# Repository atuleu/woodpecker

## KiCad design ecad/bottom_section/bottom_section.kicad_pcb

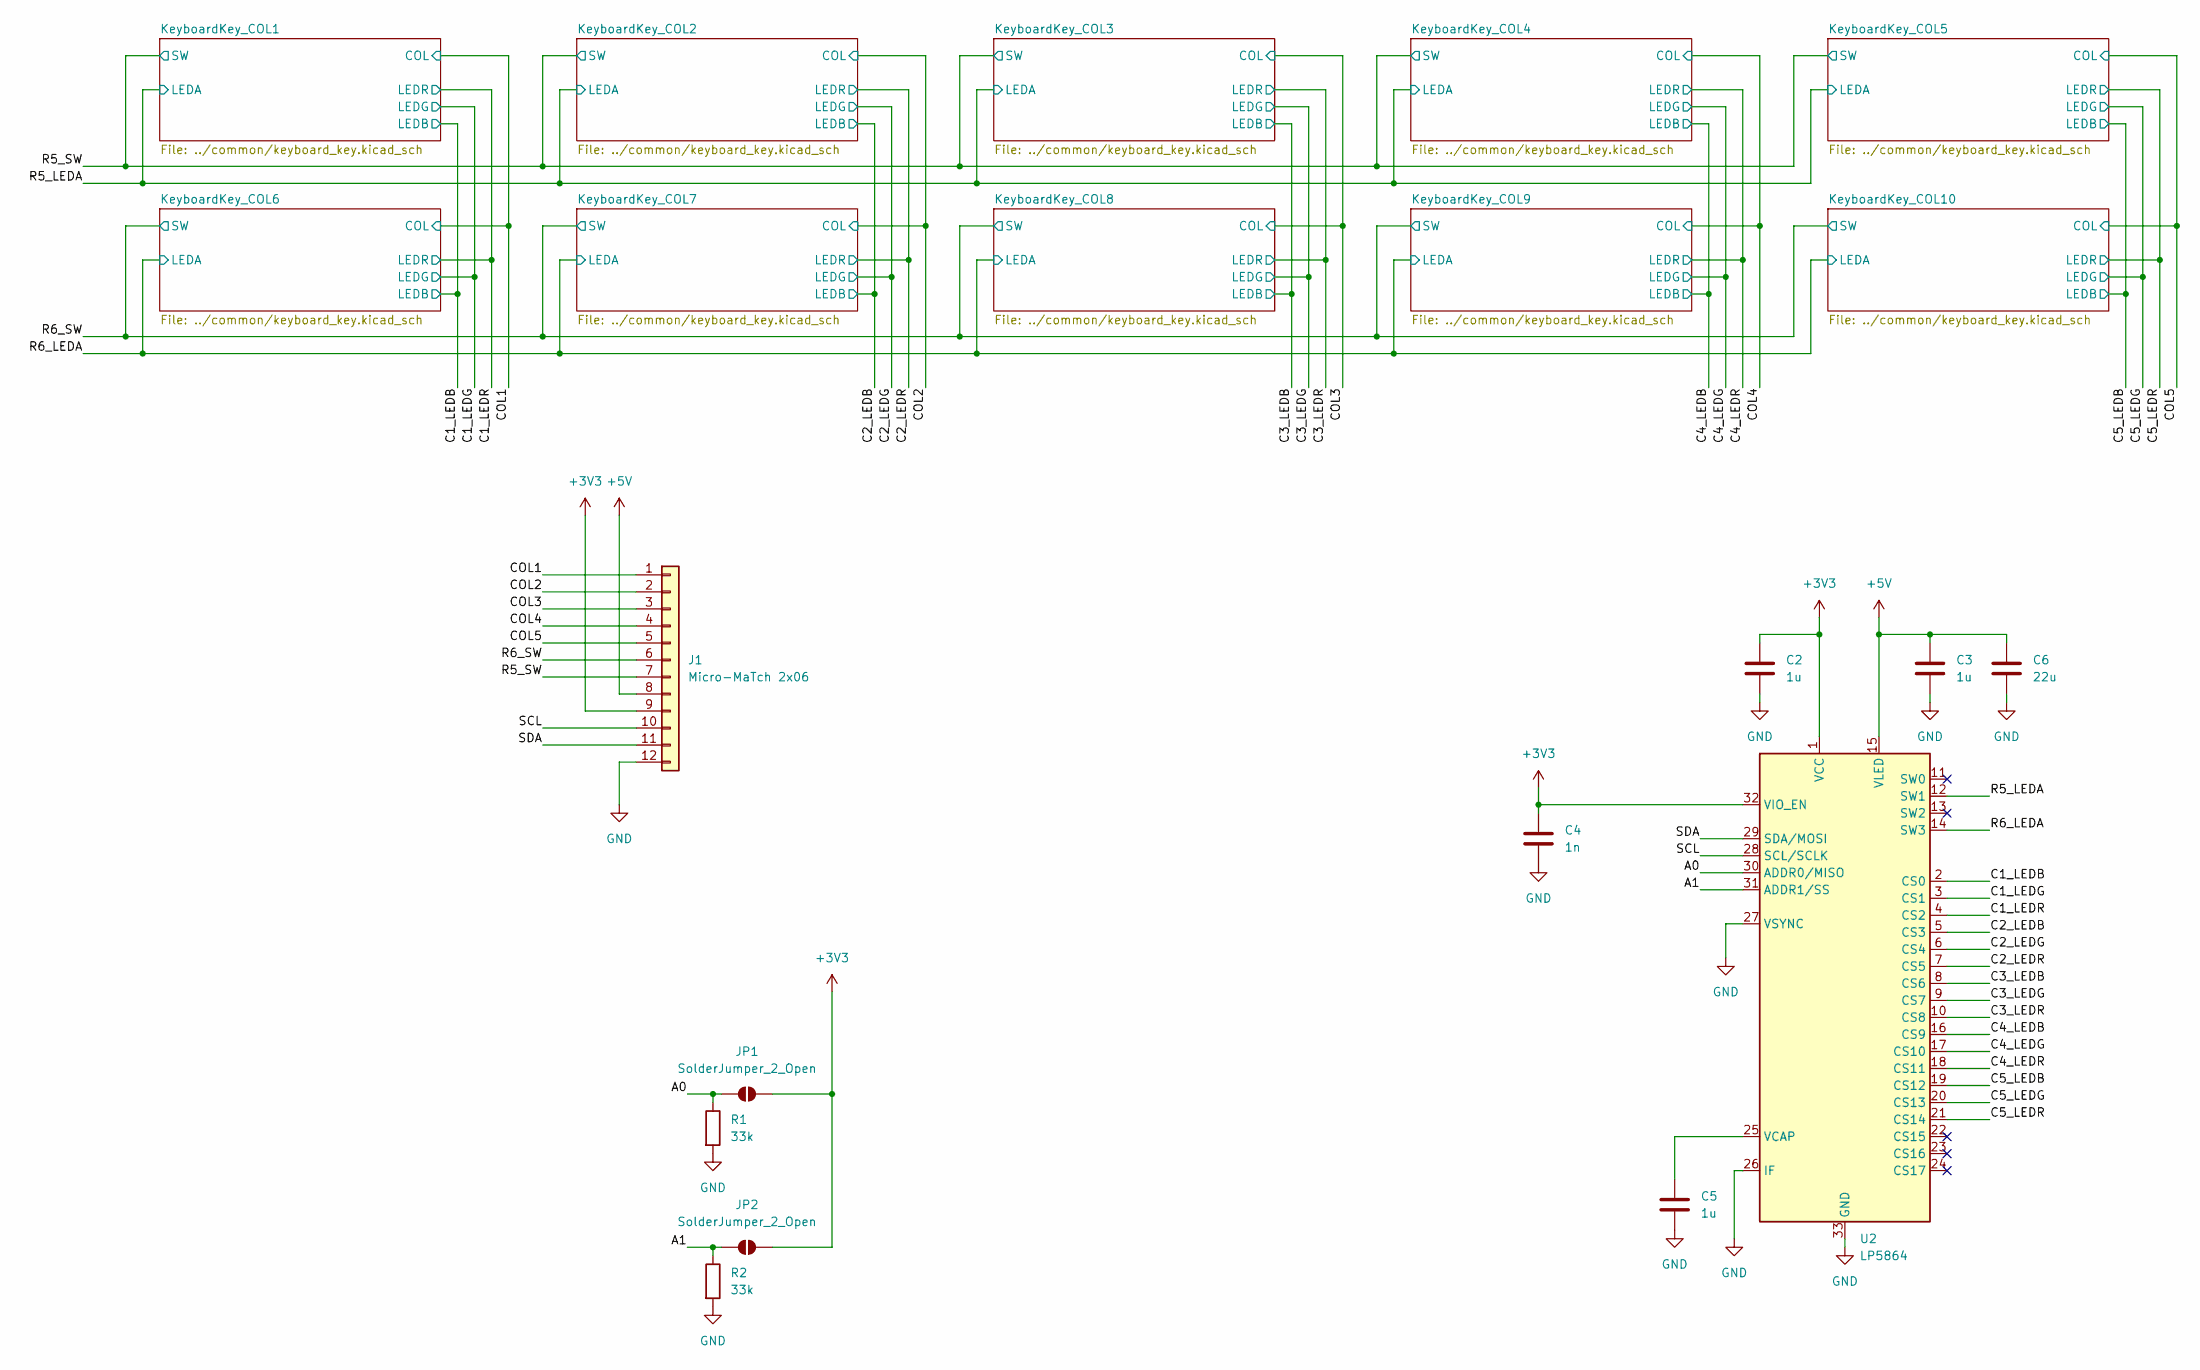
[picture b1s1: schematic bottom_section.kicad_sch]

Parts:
C2, C3, C5: 1u; C_0402_1005Metric; MPN GCM155C71A105KE38D
C4: 1n; C_0402_1005Metric; MPN KGM05AR71A102KH
C6: 22u; C_0805_2012Metric; MPN GRM21BZ71A226ME15L
J1: Micro-MaTch 2x06; TE_Micro-MaTch_1-215079-2_2x06_P1.27mm_Vertical; MPN 1-215079-2
JP1, JP2: SolderJumper_2_Open; SolderJumper-2_P1.3mm_Open_TrianglePad1.0x1.5mm
R1, R2: 33k; R_0603_1608Metric; MPN RC0603FR-0733KL
U2: LP5864; Texas_LP586X_VQFN-32-1EP_4x4mm_P0.4mm_EP2.8x2.8mm_ThermalVi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; MPN LP5864RSMR

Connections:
+3V3: C2.1, C4.1, J1.9, JP1.2 (B), JP2.2 (B), U2.1 (VCC), U2.32 (VIO_EN)
+5V: C3.1, C6.1, J1.8, U2.15 (VLED)
/A0: JP1.1 (A), R1.1, U2.30 (ADDR0/MISO)
/A1: JP2.1 (A), R2.1, U2.31 (ADDR1/SS)
/C1_LEDB: U2.2 (CS0); also elsewhere on the board
/C1_LEDG: U2.3 (CS1); also elsewhere on the board
/C1_LEDR: U2.4 (CS2); also elsewhere on the board
/C2_LEDB: U2.5 (CS3); also elsewhere on the board
/C2_LEDG: U2.6 (CS4); also elsewhere on the board
/C2_LEDR: U2.7 (CS5); also elsewhere on the board
/C3_LEDB: U2.8 (CS6); also elsewhere on the board
/C3_LEDG: U2.9 (CS7); also elsewhere on the board
/C3_LEDR: U2.10 (CS8); also elsewhere on the board
/C4_LEDB: U2.16 (CS9); also elsewhere on the board
/C4_LEDG: U2.17 (CS10); also elsewhere on the board
/C4_LEDR: U2.18 (CS11); also elsewhere on the board
/C5_LEDB: U2.19 (CS12); also elsewhere on the board
/C5_LEDG: U2.20 (CS13); also elsewhere on the board
/C5_LEDR: U2.21 (CS14); also elsewhere on the board
/COL1: J1.1; also elsewhere on the board
/COL2: J1.2; also elsewhere on the board
/COL3: J1.3; also elsewhere on the board
/COL4: J1.4; also elsewhere on the board
/COL5: J1.5; also elsewhere on the board
/R5_LEDA: U2.12 (SW1); also elsewhere on the board
/R5_SW: J1.7; also elsewhere on the board
/R6_LEDA: U2.14 (SW3); also elsewhere on the board
/R6_SW: J1.6; also elsewhere on the board
/SCL: J1.10, U2.28 (SCL/SCLK)
/SDA: J1.11, U2.29 (SDA/MOSI)
GND: C2.2, C3.2, C4.2, C5.2, C6.2, J1.12, R1.2, R2.2, U2.26 (IF), U2.27 (VSYNC), U2.33 (GND)
unnamed: C5.1, U2.25 (VCAP)

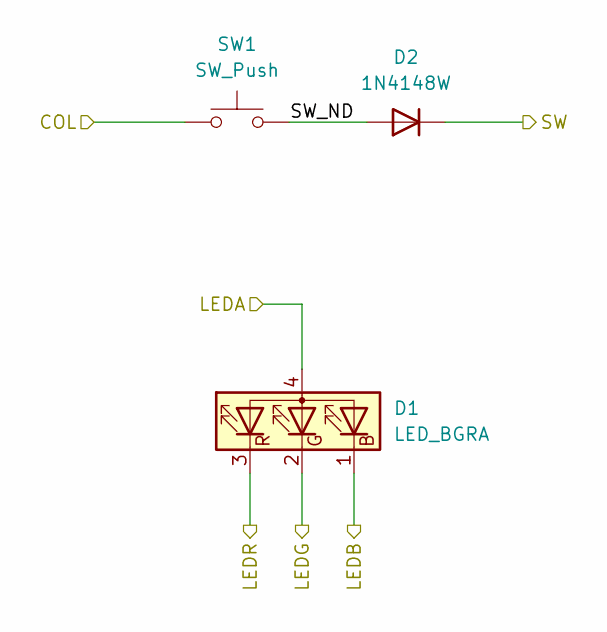
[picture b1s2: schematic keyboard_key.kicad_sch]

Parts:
D1: LED_BGRA; LED_Inolux_IN-PI32TRRRGB_PLCC4_3.2x2.8mm_P1.5mm; MPN IN-P32TRRRGB
D2: 1N4148W; D_SOD-123; MPN 1N4148W
SW1: SW_Push; SW_Hotswap_Kailh_MX_1.00u; MPN 1528-5118-ND

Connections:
/C1_LEDB: D1.1 (BK); also elsewhere on the board
/C1_LEDG: D1.2 (GK); also elsewhere on the board
/C1_LEDR: D1.3 (RK); also elsewhere on the board
/COL1: SW1.1; also elsewhere on the board
/KeyboardKey_COL1/SW_ND: D2.2 (A), SW1.2
/R5_LEDA: D1.4 (A); also elsewhere on the board
/R5_SW: D2.1 (K); also elsewhere on the board

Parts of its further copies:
D4, D6, D8, D10, D12, D14, D16, D18, D20: 1N4148W; D_SOD-123; MPN 1N4148W
D5, D7, D9, D11, D13, D15, D17, D19: LED_BGRA; LED_Inolux_IN-PI32TRRRGB_PLCC4_3.2x2.8mm_P1.5mm; MPN IN-P32TRRRGB
SW2, SW3, SW4, SW5, SW6, SW7, SW8, SW9, SW10: SW_Push; SW_Hotswap_Kailh_MX_1.00u; MPN 1528-5118-ND

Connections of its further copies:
/C1_LEDB: D11.1 (BK); also elsewhere on the board
/C1_LEDG: D11.2 (GK); also elsewhere on the board
/C1_LEDR: D11.3 (RK); also elsewhere on the board
/C2_LEDB: D13.1 (BK); also elsewhere on the board
/C2_LEDG: D13.2 (GK); also elsewhere on the board
/C2_LEDR: D13.3 (RK); also elsewhere on the board
/C3_LEDB: D5.1 (BK), D15.1 (BK); also elsewhere on the board
/C3_LEDG: D5.2 (GK), D15.2 (GK); also elsewhere on the board
/C3_LEDR: D5.3 (RK), D15.3 (RK); also elsewhere on the board
/C4_LEDB: D7.1 (BK), D17.1 (BK); also elsewhere on the board
/C4_LEDG: D7.2 (GK), D17.2 (GK); also elsewhere on the board
/C4_LEDR: D7.3 (RK), D17.3 (RK); also elsewhere on the board
/C5_LEDB: D9.1 (BK), D19.1 (BK); also elsewhere on the board
/C5_LEDG: D9.2 (GK), D19.2 (GK); also elsewhere on the board
/C5_LEDR: D9.3 (RK), D19.3 (RK); also elsewhere on the board
/COL1: SW6.1; also elsewhere on the board
/COL2: SW2.1, SW7.1; also elsewhere on the board
/COL3: SW3.1, SW8.1; also elsewhere on the board
/COL4: SW4.1, SW9.1; also elsewhere on the board
/COL5: SW5.1, SW10.1; also elsewhere on the board
/KeyboardKey_COL2/SW_ND: D4.2 (A), SW2.2
/KeyboardKey_COL3/SW_ND: D6.2 (A), SW3.2
/KeyboardKey_COL4/SW_ND: D8.2 (A), SW4.2
/KeyboardKey_COL5/SW_ND: D10.2 (A), SW5.2
/KeyboardKey_COL6/SW_ND: D12.2 (A), SW6.2
/KeyboardKey_COL7/SW_ND: D14.2 (A), SW7.2
/KeyboardKey_COL8/SW_ND: D16.2 (A), SW8.2
/KeyboardKey_COL9/SW_ND: D18.2 (A), SW9.2
/KeyboardKey_COL10/SW_ND: D20.2 (A), SW10.2
/R5_LEDA: D5.4 (A), D7.4 (A), D9.4 (A); also elsewhere on the board
/R5_SW: D4.1 (K), D6.1 (K), D8.1 (K), D10.1 (K); also elsewhere on the board
/R6_LEDA: D11.4 (A), D13.4 (A), D15.4 (A), D17.4 (A), D19.4 (A); also elsewhere on the board
/R6_SW: D12.1 (K), D14.1 (K), D16.1 (K), D18.1 (K), D20.1 (K); also elsewhere on the board

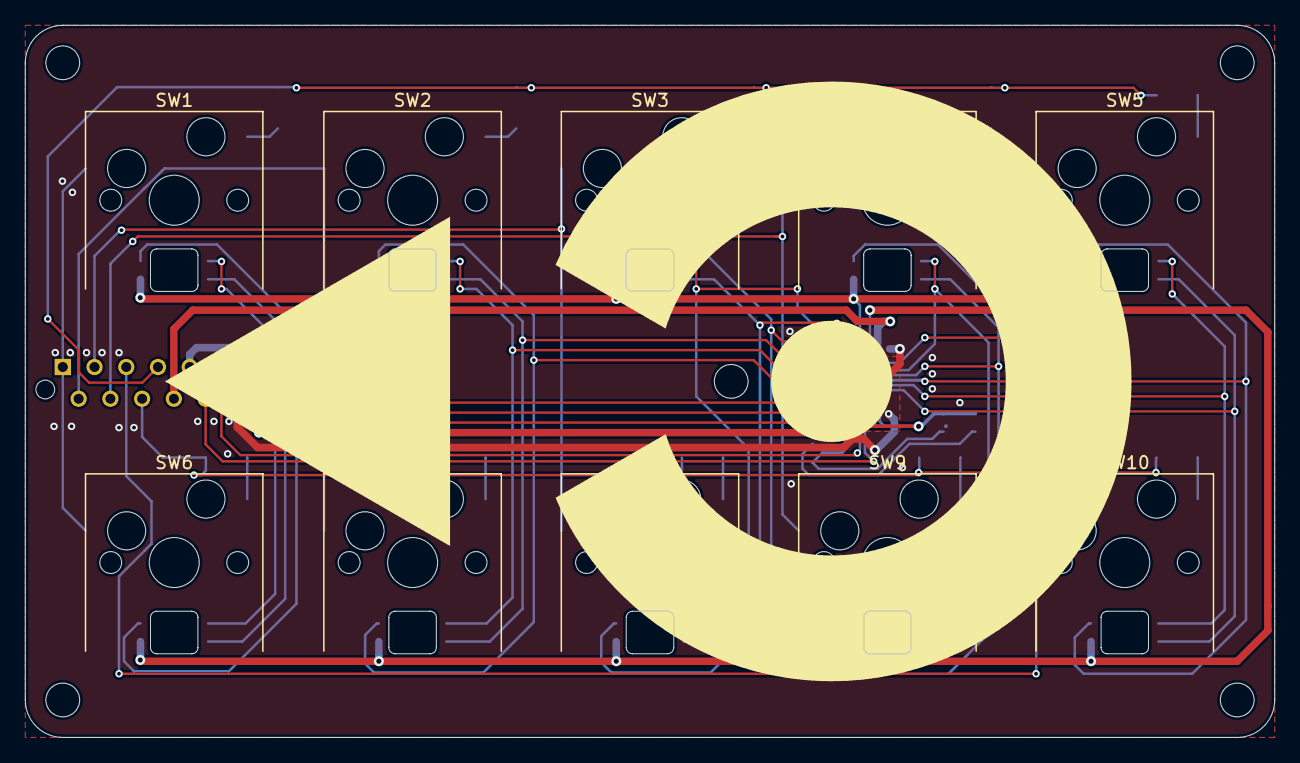
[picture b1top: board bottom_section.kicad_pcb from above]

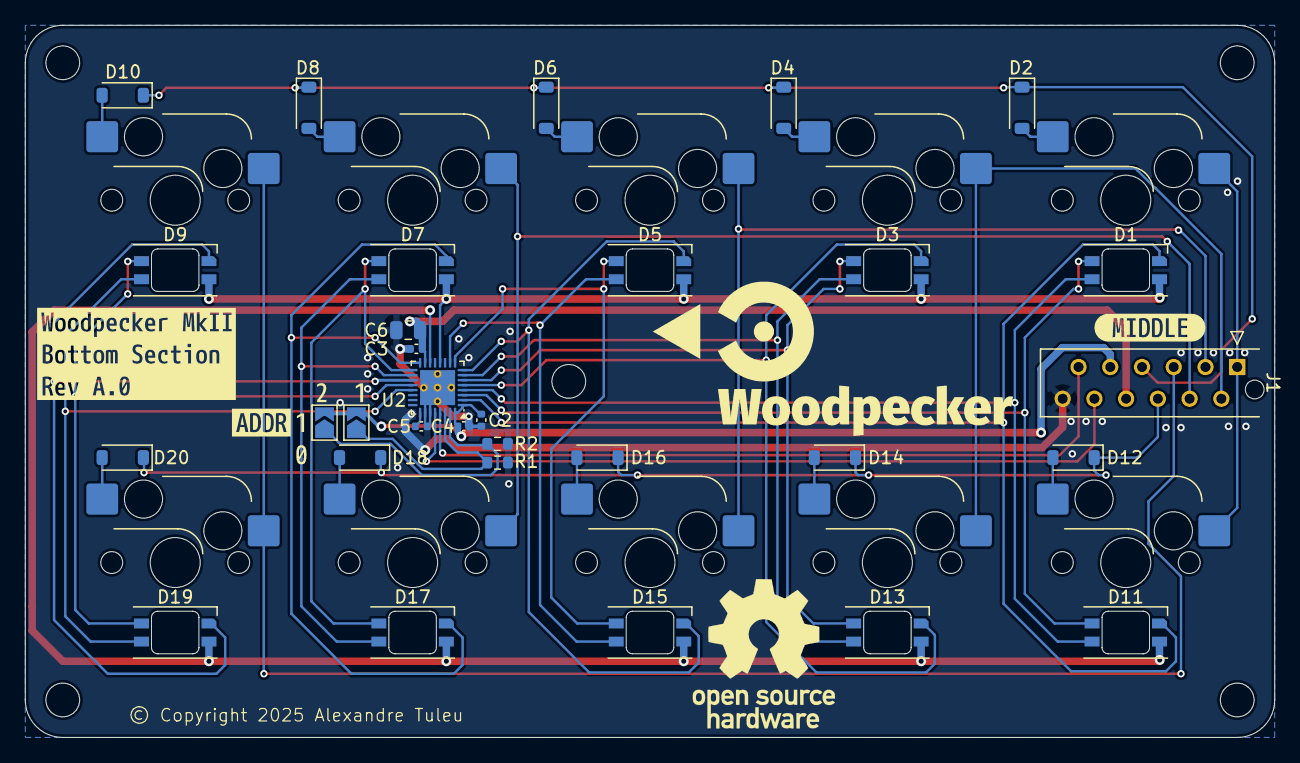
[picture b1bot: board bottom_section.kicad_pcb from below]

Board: 2 copper layers, 100.0 x 57.0 mm, 46 parts (36 on the bottom side), 42 nets.

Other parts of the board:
D3: LED_BGRA; LED_Inolux_IN-PI32TRRRGB_PLCC4_3.2x2.8mm_P1.5mm
kibuzzard-68CC27A1: G***; kibuzzard-68CC27A1
kibuzzard-68CC27B2: G***; kibuzzard-68CC27B2
kibuzzard-68CC27E6: G***; kibuzzard-68CC27E6
kibuzzard-68CC277E: G***; kibuzzard-68CC277E
kibuzzard-68CC2926: G***; kibuzzard-68CC2926

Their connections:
/C2_LEDB: D3.1 (BK); also elsewhere on the board
/C2_LEDG: D3.2 (GK); also elsewhere on the board
/C2_LEDR: D3.3 (RK); also elsewhere on the board
/R5_LEDA: D3.4 (A); also elsewhere on the board

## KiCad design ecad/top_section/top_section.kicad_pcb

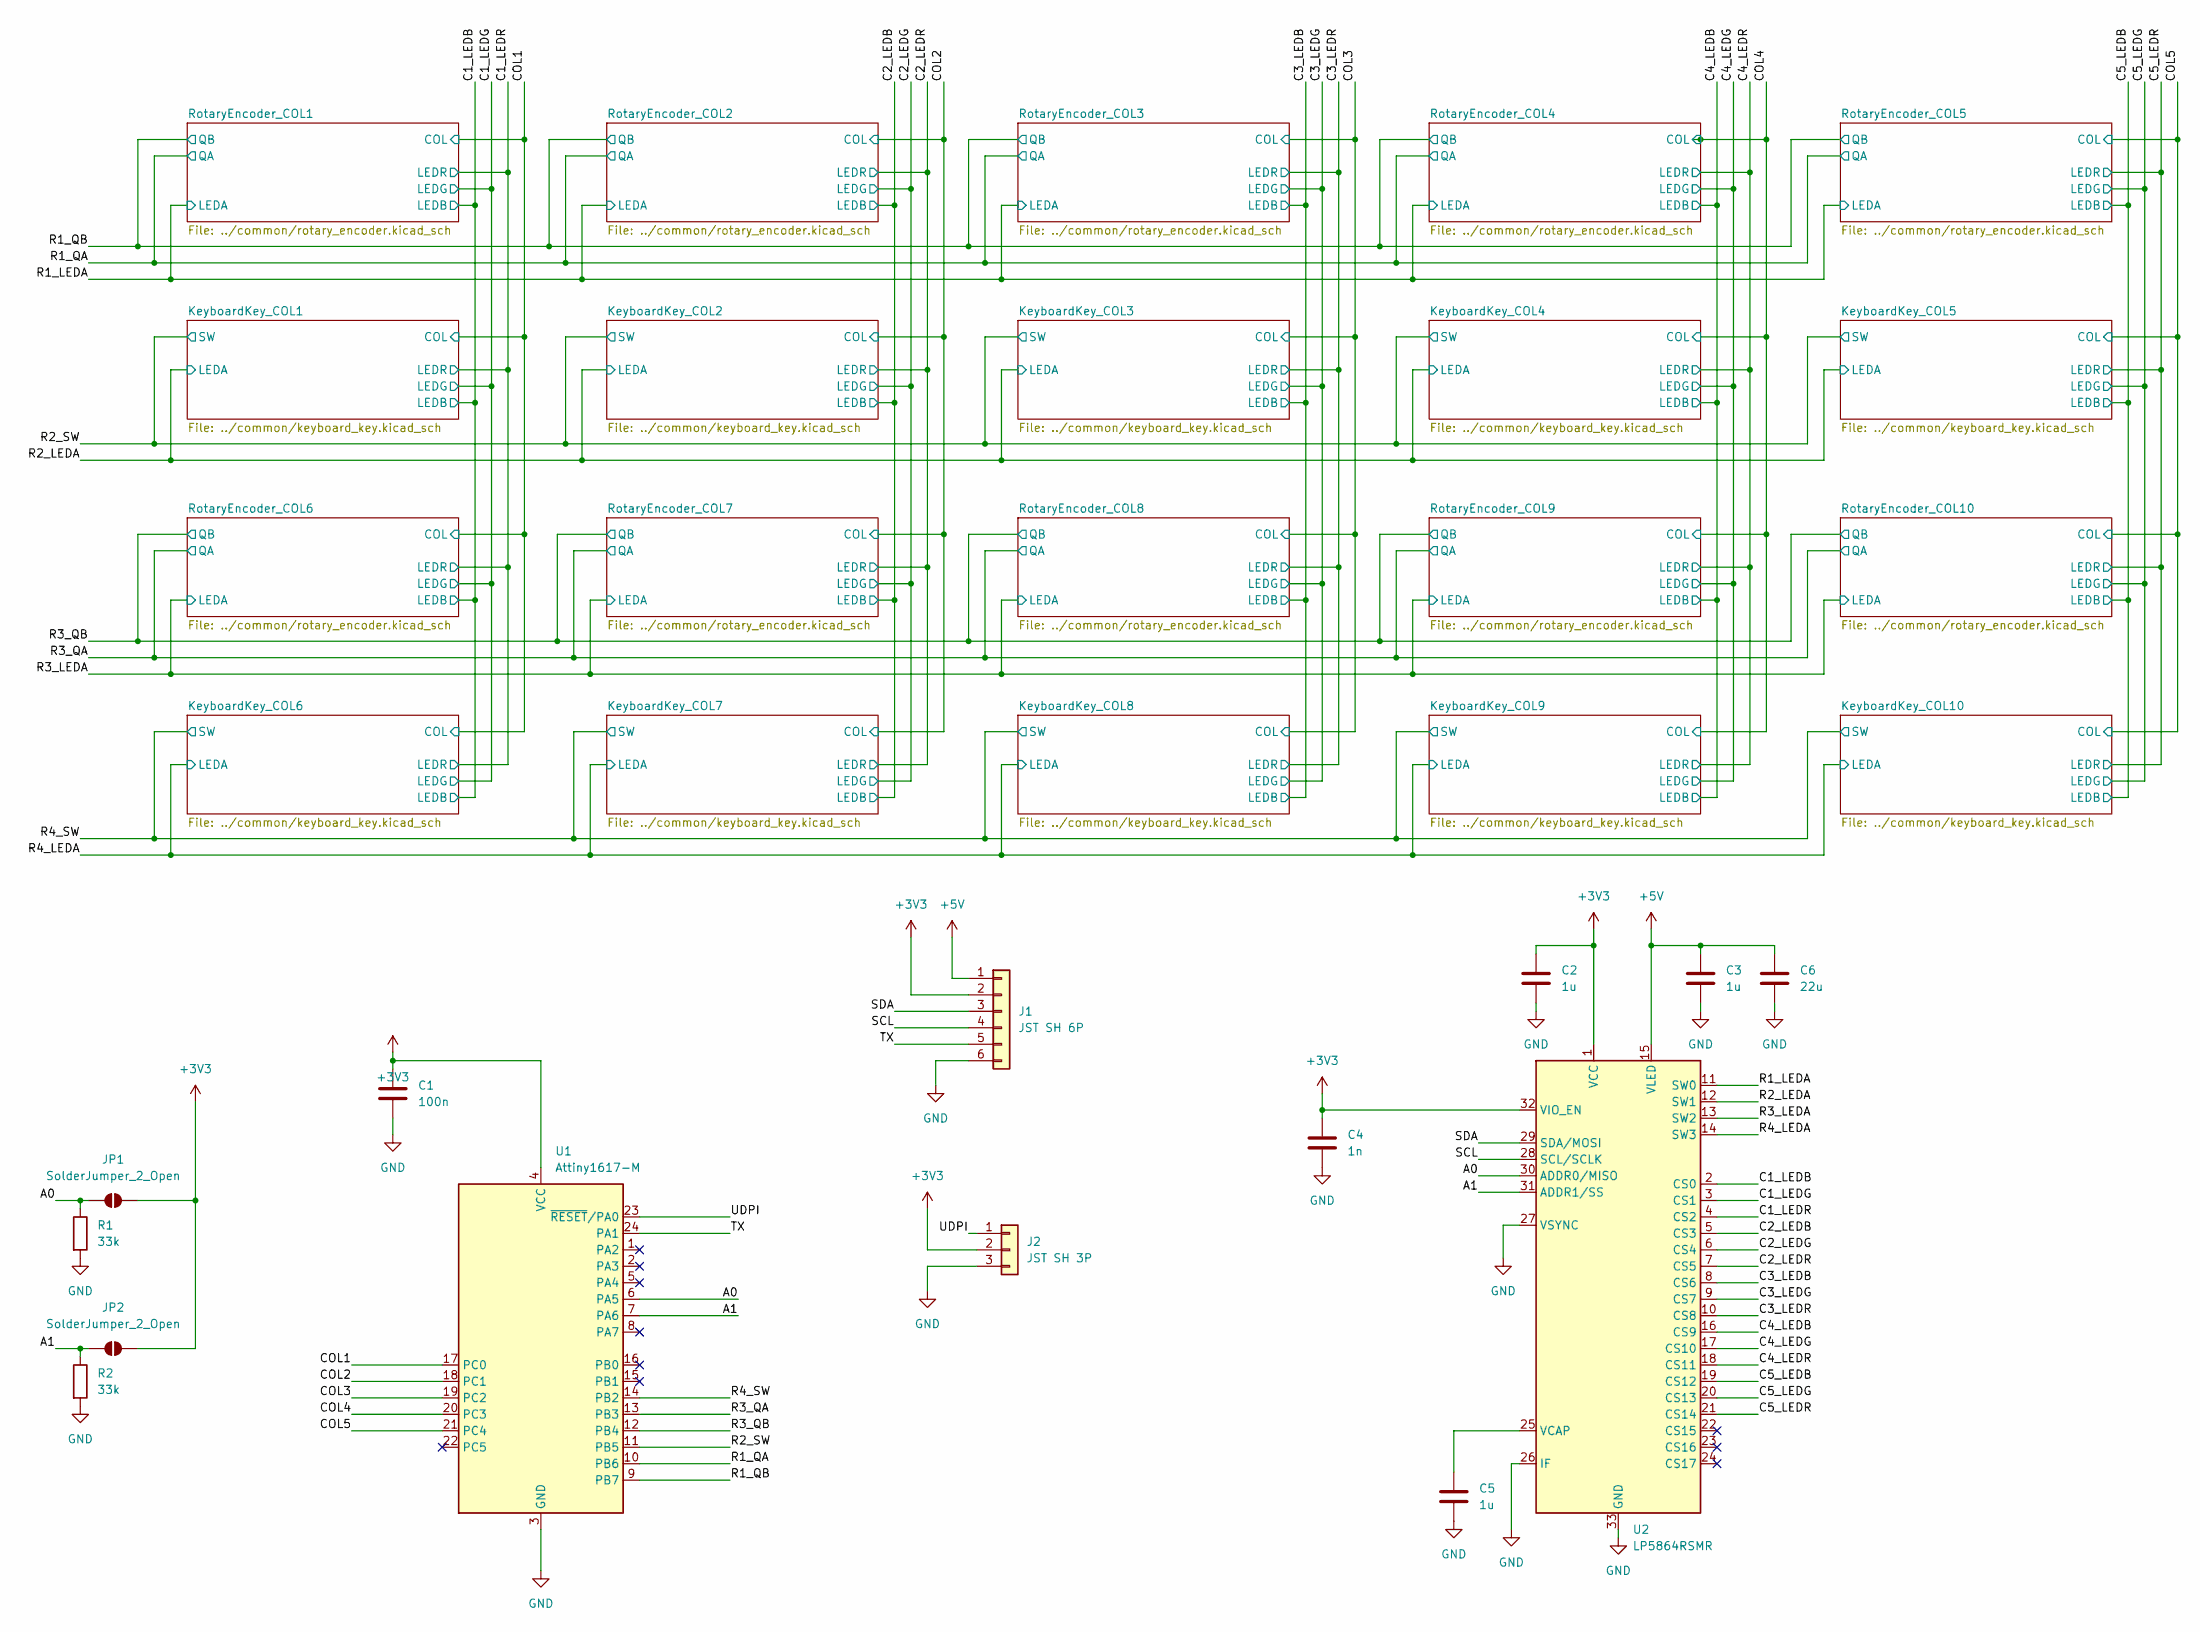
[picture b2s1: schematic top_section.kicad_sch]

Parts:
C1: 100n; C_0603_1608Metric; MPN CL10B104KB8NNWC
C2, C3, C5: 1u; C_0402_1005Metric; MPN GCM155C71A105KE38D
C4: 1n; C_0402_1005Metric; MPN KGM05AR71A102KH
C6: 22u; C_0805_2012Metric; MPN GRM21BZ71A226ME15L
J1: JST SH 6P; JST_SH_SM06B-SRSS-TB_1x06-1MP_P1.00mm_Horizontal; MPN SM06B-SRSS-TB
J2: JST SH 3P; JST_SH_SM03B-SRSS-TB_1x03-1MP_P1.00mm_Horizontal; MPN SM03B-SRSS-TB
JP1, JP2: SolderJumper_2_Open; SolderJumper-2_P1.3mm_Open_TrianglePad1.0x1.5mm
R1, R2: 33k; R_0603_1608Metric; MPN RC0603FR-0733KL
U1: Attiny1617-M; QFN-24-1EP_4x4mm_P0.5mm_EP2.6x2.6mm; MPN ATtiny1617-MNR
U2: LP5864RSMR; Texas_LP586X_VQFN-32-1EP_4x4mm_P0.4mm_EP2.8x2.8mm_ThermalVi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; MPN LP5864RSMR

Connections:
+3V3: C1.1, C2.1, C4.1, J1.2, J2.2, JP1.2 (B), JP2.2 (B), U1.4 (VCC), U2.1 (VCC), U2.32 (VIO_EN)
+5V: C3.1, C6.1, J1.1, U2.15 (VLED)
/A0: JP1.1 (A), R1.1, U1.6 (PA5), U2.30 (ADDR0/MISO)
/A1: JP2.1 (A), R2.1, U1.7 (PA6), U2.31 (ADDR1/SS)
/C1_LEDB: U2.2 (CS0); also elsewhere on the board
/C1_LEDG: U2.3 (CS1); also elsewhere on the board
/C1_LEDR: U2.4 (CS2); also elsewhere on the board
/C2_LEDB: U2.5 (CS3); also elsewhere on the board
/C2_LEDG: U2.6 (CS4); also elsewhere on the board
/C2_LEDR: U2.7 (CS5); also elsewhere on the board
/C3_LEDB: U2.8 (CS6); also elsewhere on the board
/C3_LEDG: U2.9 (CS7); also elsewhere on the board
/C3_LEDR: U2.10 (CS8); also elsewhere on the board
/C4_LEDB: U2.16 (CS9); also elsewhere on the board
/C4_LEDG: U2.17 (CS10); also elsewhere on the board
/C4_LEDR: U2.18 (CS11); also elsewhere on the board
/C5_LEDB: U2.19 (CS12); also elsewhere on the board
/C5_LEDG: U2.20 (CS13); also elsewhere on the board
/C5_LEDR: U2.21 (CS14); also elsewhere on the board
/COL1: U1.17 (PC0); also elsewhere on the board
/COL2: U1.18 (PC1); also elsewhere on the board
/COL3: U1.19 (PC2); also elsewhere on the board
/COL4: U1.20 (PC3); also elsewhere on the board
/COL5: U1.21 (PC4); also elsewhere on the board
/R1_LEDA: U2.11 (SW0); also elsewhere on the board
/R1_QA: U1.10 (PB6); also elsewhere on the board
/R1_QB: U1.9 (PB7); also elsewhere on the board
/R2_LEDA: U2.12 (SW1); also elsewhere on the board
/R2_SW: U1.11 (PB5); also elsewhere on the board
/R3_LEDA: U2.13 (SW2); also elsewhere on the board
/R3_QA: U1.13 (PB3); also elsewhere on the board
/R3_QB: U1.12 (PB4); also elsewhere on the board
/R4_LEDA: U2.14 (SW3); also elsewhere on the board
/R4_SW: U1.14 (PB2); also elsewhere on the board
/SCL: J1.4, U2.28 (SCL/SCLK)
/SDA: J1.3, U2.29 (SDA/MOSI)
/TX: J1.5, U1.24 (PA1)
/UDPI: J2.1, U1.23 (~RESET/PA0)
GND: C1.2, C2.2, C3.2, C4.2, C5.2, C6.2, J1.6, J2.3, R1.2, R2.2, U1.3 (GND), U1.25 (GND), U2.26 (IF), U2.27 (VSYNC), U2.33 (GND)
unnamed: C5.1, U2.25 (VCAP)

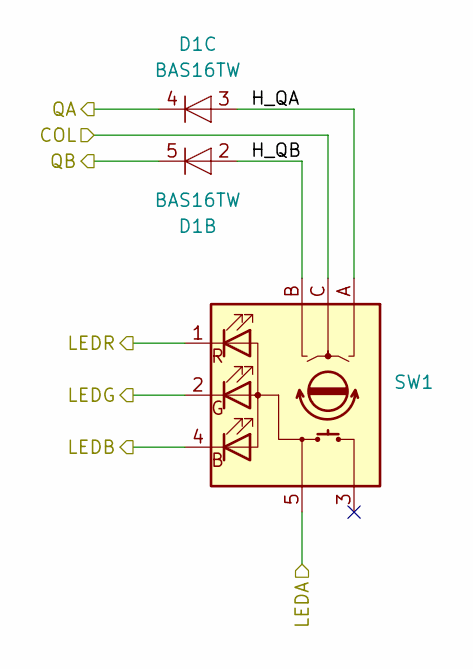
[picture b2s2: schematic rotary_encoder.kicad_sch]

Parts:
D1: BAS16TW; SOT-363_SC-70-6; MPN BAS16TW
SW1: PEL12T; PEL12T-4xxxS-S1024; MPN PEL12T-4225S-S1024

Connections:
/C1_LEDB: SW1.4 (BK); also elsewhere on the board
/C1_LEDG: SW1.2 (GK); also elsewhere on the board
/C1_LEDR: SW1.1 (RK); also elsewhere on the board
/COL1: SW1.C; also elsewhere on the board
/R1_LEDA: SW1.5 (A); also elsewhere on the board
/R1_QA: D1.4 (K); also elsewhere on the board
/R1_QB: D1.5 (K); also elsewhere on the board
/RotaryEncoder_COL1/H_QA: D1.3 (A), SW1.A
/RotaryEncoder_COL1/H_QB: D1.2 (A), SW1.B

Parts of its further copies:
D4, D5, D6, D7, D8, D27, D28, D29, D30: BAS16TW; SOT-363_SC-70-6; MPN BAS16TW
SW3, SW4, SW5, SW6, SW7, SW17, SW18, SW19, SW20: PEL12T; PEL12T-4xxxS-S1024; MPN PEL12T-4225S-S1024

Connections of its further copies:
/C1_LEDB: SW7.4 (BK); also elsewhere on the board
/C1_LEDG: SW7.2 (GK); also elsewhere on the board
/C1_LEDR: SW7.1 (RK); also elsewhere on the board
/C2_LEDB: SW3.4 (BK), SW17.4 (BK); also elsewhere on the board
/C2_LEDG: SW3.2 (GK), SW17.2 (GK); also elsewhere on the board
/C2_LEDR: SW3.1 (RK), SW17.1 (RK); also elsewhere on the board
/C3_LEDB: SW4.4 (BK), SW18.4 (BK); also elsewhere on the board
/C3_LEDG: SW4.2 (GK), SW18.2 (GK); also elsewhere on the board
/C3_LEDR: SW4.1 (RK), SW18.1 (RK); also elsewhere on the board
/C4_LEDB: SW5.4 (BK), SW19.4 (BK); also elsewhere on the board
/C4_LEDG: SW5.2 (GK), SW19.2 (GK); also elsewhere on the board
/C4_LEDR: SW5.1 (RK), SW19.1 (RK); also elsewhere on the board
/C5_LEDB: SW6.4 (BK), SW20.4 (BK); also elsewhere on the board
/C5_LEDG: SW6.2 (GK), SW20.2 (GK); also elsewhere on the board
/C5_LEDR: SW6.1 (RK), SW20.1 (RK); also elsewhere on the board
/COL1: SW7.C; also elsewhere on the board
/COL2: SW3.C, SW17.C; also elsewhere on the board
/COL3: SW4.C, SW18.C; also elsewhere on the board
/COL4: SW5.C, SW19.C; also elsewhere on the board
/COL5: SW6.C, SW20.C; also elsewhere on the board
/R1_LEDA: SW3.5 (A), SW4.5 (A), SW5.5 (A), SW6.5 (A); also elsewhere on the board
/R1_QA: D4.4 (K), D5.4 (K), D6.4 (K), D7.4 (K); also elsewhere on the board
/R1_QB: D4.5 (K), D5.5 (K), D6.5 (K), D7.5 (K); also elsewhere on the board
/R3_LEDA: SW7.5 (A), SW17.5 (A), SW18.5 (A), SW19.5 (A), SW20.5 (A); also elsewhere on the board
/R3_QA: D8.4 (K), D27.4 (K), D28.4 (K), D29.4 (K), D30.4 (K); also elsewhere on the board
/R3_QB: D8.5 (K), D27.5 (K), D28.5 (K), D29.5 (K), D30.5 (K); also elsewhere on the board
/RotaryEncoder_COL2/H_QA: D4.3 (A), SW3.A
/RotaryEncoder_COL2/H_QB: D4.2 (A), SW3.B
/RotaryEncoder_COL3/H_QA: D5.3 (A), SW4.A
/RotaryEncoder_COL3/H_QB: D5.2 (A), SW4.B
/RotaryEncoder_COL4/H_QA: D6.3 (A), SW5.A
/RotaryEncoder_COL4/H_QB: D6.2 (A), SW5.B
/RotaryEncoder_COL5/H_QA: D7.3 (A), SW6.A
/RotaryEncoder_COL5/H_QB: D7.2 (A), SW6.B
/RotaryEncoder_COL6/H_QA: D8.3 (A), SW7.A
/RotaryEncoder_COL6/H_QB: D8.2 (A), SW7.B
/RotaryEncoder_COL7/H_QA: D27.3 (A), SW17.A
/RotaryEncoder_COL7/H_QB: D27.2 (A), SW17.B
/RotaryEncoder_COL8/H_QA: D28.3 (A), SW18.A
/RotaryEncoder_COL8/H_QB: D28.2 (A), SW18.B
/RotaryEncoder_COL9/H_QA: D29.3 (A), SW19.A
/RotaryEncoder_COL9/H_QB: D29.2 (A), SW19.B
/RotaryEncoder_COL10/H_QA: D30.3 (A), SW20.A
/RotaryEncoder_COL10/H_QB: D30.2 (A), SW20.B

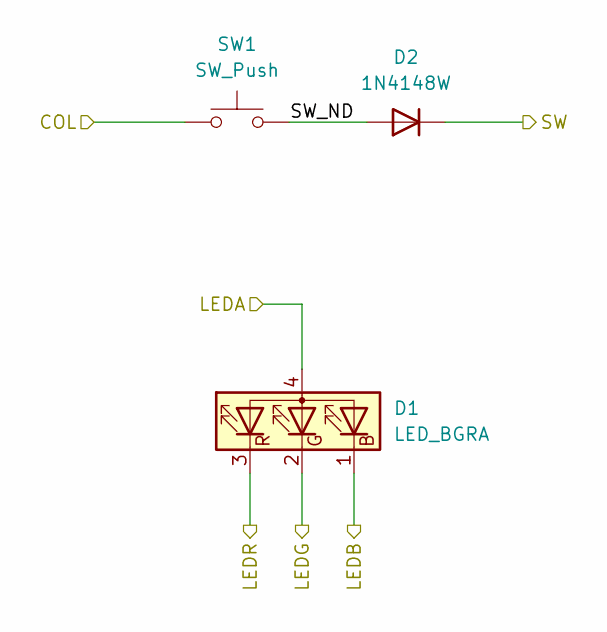
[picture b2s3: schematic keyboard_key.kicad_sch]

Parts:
D1: LED_BGRA; LED_Inolux_IN-PI32TRRRGB_PLCC4_3.2x2.8mm_P1.5mm; MPN IN-P32TRRRGB
D2: 1N4148W; D_SOD-123; MPN 1N4148W
SW1: SW_Push; SW_Hotswap_Kailh_MX_1.00u; MPN 1528-5118-ND

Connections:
/C1_LEDB: D2.1 (BK); also elsewhere on the board
/C1_LEDG: D2.2 (GK), SW1.2 (GK); also elsewhere on the board
/C1_LEDR: D2.3 (RK), SW1.1 (RK); also elsewhere on the board
/R1_QA: D1.4 (K); also elsewhere on the board
/R2_LEDA: D2.4 (A); also elsewhere on the board
/RotaryEncoder_COL1/H_QA: D1.3 (A); also elsewhere on the board
/RotaryEncoder_COL1/H_QB: D1.2 (A); also elsewhere on the board

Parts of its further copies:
D3, D10, D12, D14, D16, D18, D20, D22, D24, D26: 1N4148W; D_SOD-123; MPN 1N4148W
D9, D11, D13, D15, D17, D19, D21, D23, D25: LED_BGRA; LED_Inolux_IN-PI32TRRRGB_PLCC4_3.2x2.8mm_P1.5mm; MPN IN-P32TRRRGB
SW2, SW8, SW9, SW10, SW11, SW12, SW13, SW14, SW15, SW16: SW_Push; SW_Hotswap_Kailh_MX_1.00u; MPN 1528-5118-ND

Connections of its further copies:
/C1_LEDB: D17.1 (BK); also elsewhere on the board
/C1_LEDG: D17.2 (GK); also elsewhere on the board
/C1_LEDR: D17.3 (RK); also elsewhere on the board
/C2_LEDB: D9.1 (BK), D19.1 (BK); also elsewhere on the board
/C2_LEDG: D9.2 (GK), D19.2 (GK); also elsewhere on the board
/C2_LEDR: D9.3 (RK), D19.3 (RK); also elsewhere on the board
/C3_LEDB: D11.1 (BK), D21.1 (BK); also elsewhere on the board
/C3_LEDG: D11.2 (GK), D21.2 (GK); also elsewhere on the board
/C3_LEDR: D11.3 (RK), D21.3 (RK); also elsewhere on the board
/C4_LEDB: D13.1 (BK), D23.1 (BK); also elsewhere on the board
/C4_LEDG: D13.2 (GK), D23.2 (GK); also elsewhere on the board
/C4_LEDR: D13.3 (RK), D23.3 (RK); also elsewhere on the board
/C5_LEDB: D15.1 (BK), D25.1 (BK); also elsewhere on the board
/C5_LEDG: D15.2 (GK), D25.2 (GK); also elsewhere on the board
/C5_LEDR: D15.3 (RK), D25.3 (RK); also elsewhere on the board
/COL1: SW2.1, SW12.1; also elsewhere on the board
/COL2: SW8.1, SW13.1; also elsewhere on the board
/COL3: SW9.1, SW14.1; also elsewhere on the board
/COL4: SW10.1, SW15.1; also elsewhere on the board
/COL5: SW11.1, SW16.1; also elsewhere on the board
/KeyboardKey_COL1/SW_ND: D3.2 (A), SW2.2
/KeyboardKey_COL2/SW_ND: D10.2 (A), SW8.2
/KeyboardKey_COL3/SW_ND: D12.2 (A), SW9.2
/KeyboardKey_COL4/SW_ND: D14.2 (A), SW10.2
/KeyboardKey_COL5/SW_ND: D16.2 (A), SW11.2
/KeyboardKey_COL6/SW_ND: D18.2 (A), SW12.2
/KeyboardKey_COL7/SW_ND: D20.2 (A), SW13.2
/KeyboardKey_COL8/SW_ND: D22.2 (A), SW14.2
/KeyboardKey_COL9/SW_ND: D24.2 (A), SW15.2
/KeyboardKey_COL10/SW_ND: D26.2 (A), SW16.2
/R2_LEDA: D9.4 (A), D11.4 (A), D13.4 (A), D15.4 (A); also elsewhere on the board
/R2_SW: D3.1 (K), D10.1 (K), D12.1 (K), D14.1 (K), D16.1 (K); also elsewhere on the board
/R4_LEDA: D17.4 (A), D19.4 (A), D21.4 (A), D23.4 (A), D25.4 (A); also elsewhere on the board
/R4_SW: D18.1 (K), D20.1 (K), D22.1 (K), D24.1 (K), D26.1 (K); also elsewhere on the board

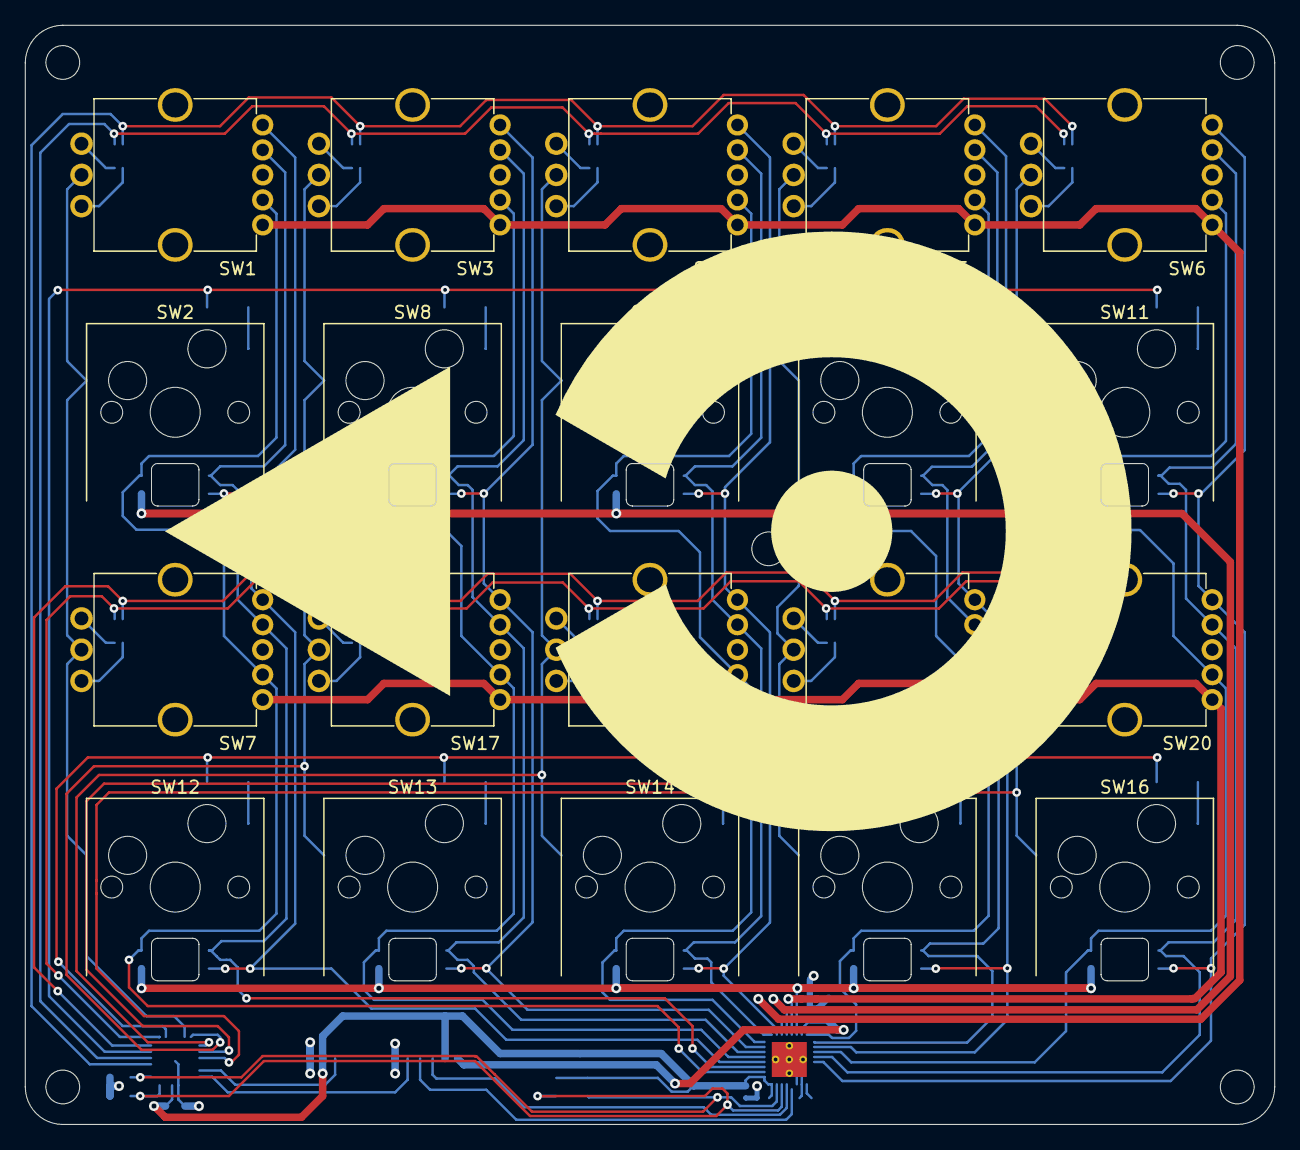
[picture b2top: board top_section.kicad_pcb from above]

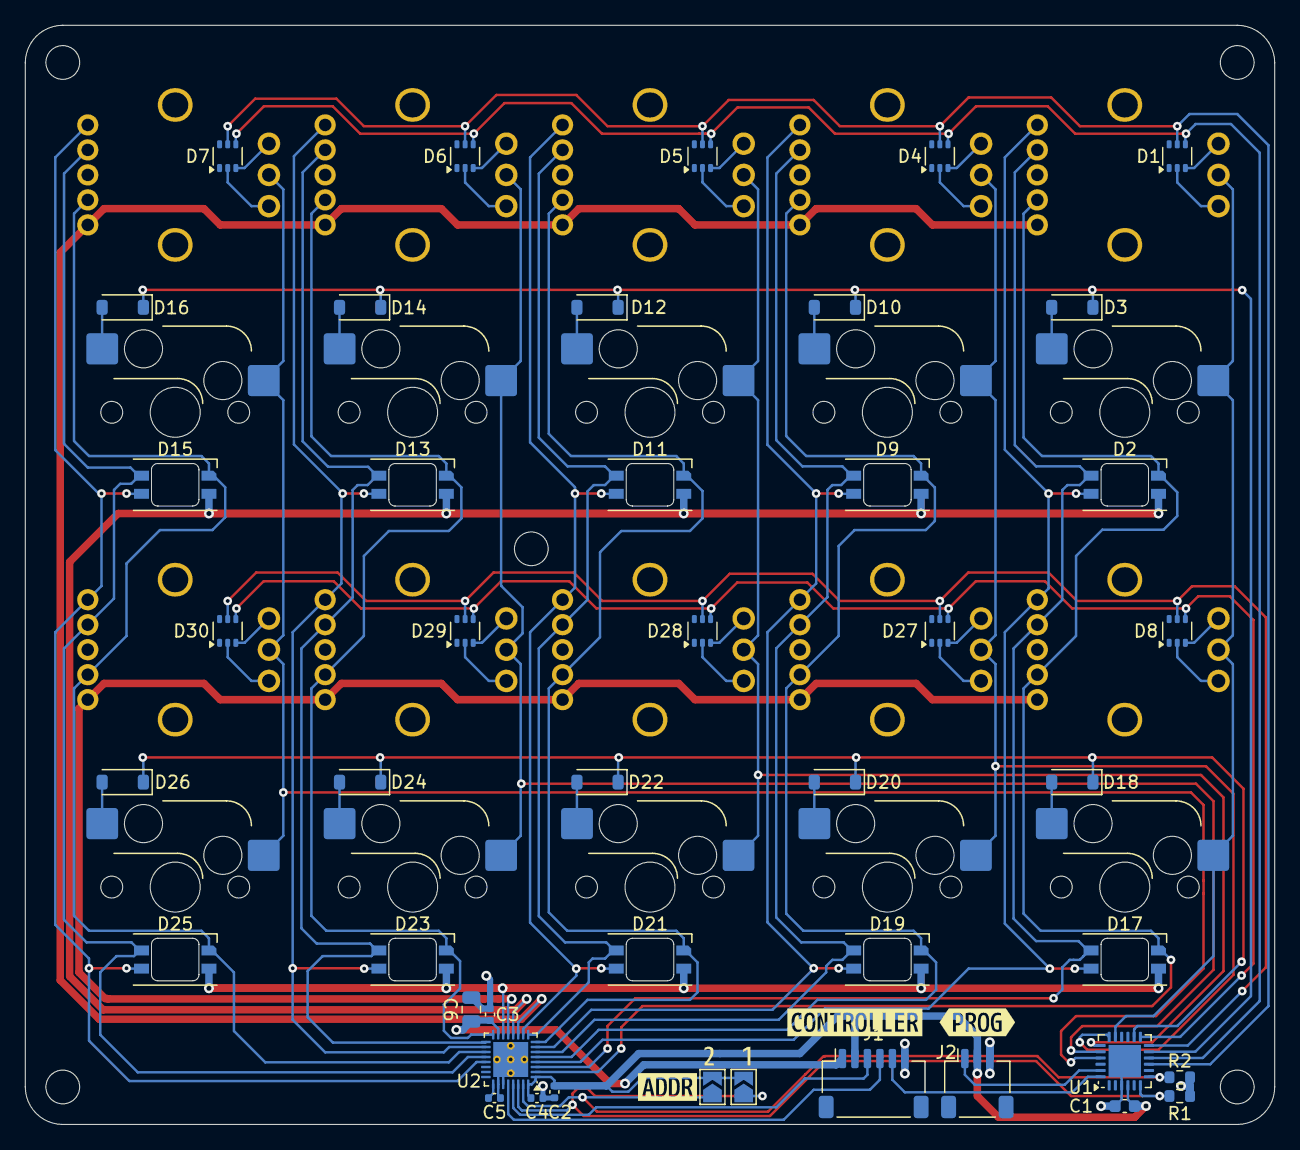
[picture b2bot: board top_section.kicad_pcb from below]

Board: 4 copper layers, 100.0 x 88.0 mm, 68 parts (48 on the bottom side), 70 nets.

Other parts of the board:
kibuzzard-68C2D999: G***; kibuzzard-68C2D999
kibuzzard-68CBF276: G***; kibuzzard-68CBF276
kibuzzard-68CC2B7E: G***; kibuzzard-68CC2B7E
kibuzzard-68CC2B91: G***; kibuzzard-68CC2B91

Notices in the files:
ecad/BottomSection/BottomSection.kicad_pcb:
© Alexandre Tuleu
ecad/bottom_section/bottom_section.kicad_pcb:
© Copyright 2025 Alexandre Tuleu
ecad/control_board/control_board.kicad_pcb:
© 2025 Alexandre Tuleu
